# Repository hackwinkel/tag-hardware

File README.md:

# tag-hardware

The "tag" is a cheap badge with a PADAUK PFS154-S16 microcontroller, 24 RGB leds and IR transmitter & receiver for inter-badge communications.
The software/hardware *may* also work with a PMS150C-S16 and pin compatible controllers from other manufacturers (e.g. Nyquest tech), but this is untested

This hardware goes with the software described here: https://github.com/hackwinkel/tag-software

## Background

This badge was originally designed for SMD hotplate soldering workshops at TBD (https://tbd.camp/) and later used for workshops at haxogreen 2024 () and private workshops, and is loosely based on a 2023 version which can be found here: https://github.com/hackwinkel/label-hardware and https://github.com/hackwinkel/label-software

According to internet rule 663829, "Every hacker conference shall have a badge". Being hackers, of course, leads to hypotheses 1-3:
"1: Any hacker conference badge will be overly complex",
"2: Any hacker conference badge will be released with unfinished software" and
"3: Any hacker conference  badge will function poorly for its namesake purpose".
This badge disproves these 3 hypotheses.

## What is in this repository

0) This README
1) a LICENSE file
2) A directory with KiCAD 5 source files
3) A directory with PCB fabrication (Gerber) files produced from these source files
4) A ZIP file containing the Gerber files for PCB fabrication.

If you only want to produce PCBs, you should be able to upload the PCB_fabrication.zip file to your PCB board house directly.
If you want to produce a single stencil, you can use  the PCB_fabrication.zip file - yoor PCB board house will extract the right file from this.

As the board only contains SMD components on the front side, you have to specify that the PCB board house should make a stencil from the "front paste" Gerber file only

## Reprogramming in-circuit

Reprogramming the processor through the programming connection may not work as expected because of failure to calibrate the clock speed while in-circuit. You CAN reprogram the badge without clock-speed calibration by using easypdkprog with the --nocalibrate option.

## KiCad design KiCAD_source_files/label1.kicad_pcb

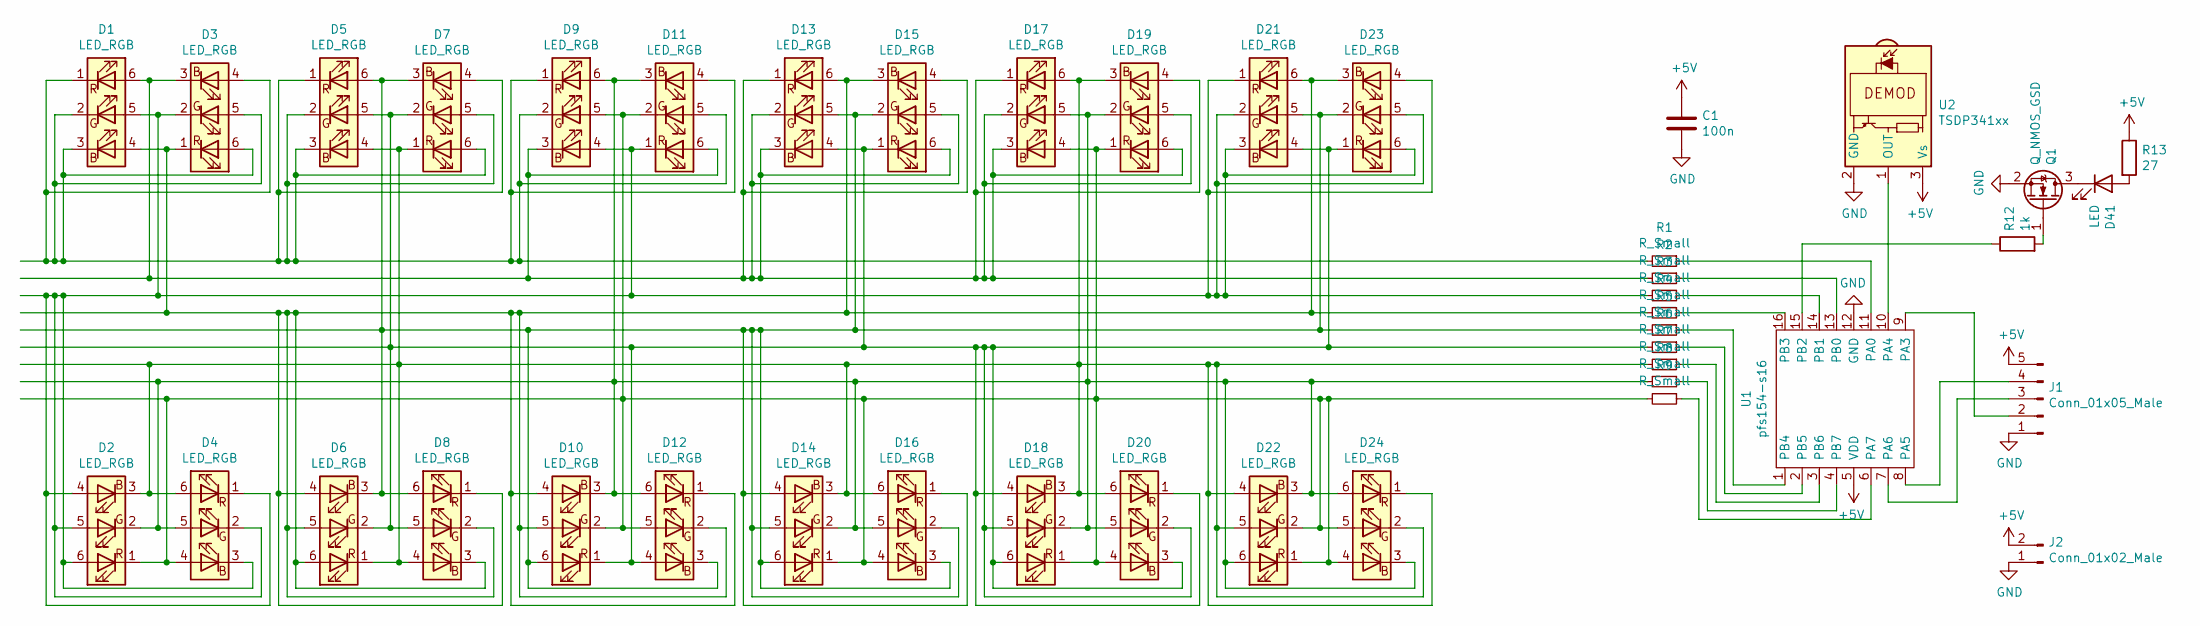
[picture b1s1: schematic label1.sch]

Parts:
C1: 100n; C_0805
D1, D2, D3, D4, D5, D6, D7, D8, D9, D10, D11, D12, D13, D14, D15, D16, D17, D18, D19, D20, D21, D22, D23, D24: LED_RGB
D41: LED; LED_3030
J1: Conn_01x05_Male; PinHeader_1x05
J2: Conn_01x02_Male; battcon
Q1: Q_NMOS_GSD; SOT-23
R1, R2, R3, R4, R5, R6, R7, R8, R9: R_Small; R_0805
R12: 1k; R_0805
R13: 27; R_1206
U1: pfs154-s16; SOP-16
U2: TSDP341xx; IR_RCV_SMD

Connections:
+5V: C1.1, J1.5, J2.2, R13.1, U1.5 (VDD), U2.3 (Vs)
GND: C1.2, J1.1, J2.1, Q1.2 (S), U1.12 (GND), U2.2 (GND)
unnamed: D1.1 (RK), D1.2 (GK), D1.3 (BK), D3.4 (BA), D3.5 (GA), D3.6 (RA), D5.1 (RK), D5.2 (GK), D5.3 (BK), D7.4 (BA), D7.5 (GA), D7.6 (RA), D9.1 (RK), D9.2 (GK), D11.4 (BA), D11.5 (GA), R1.2
unnamed: D1.4 (BA), D3.1 (RK), D6.4 (BA), D6.5 (GA), D6.6 (RA), D8.1 (RK), D8.2 (GK), D8.3 (BK), D10.4 (BA), D10.5 (GA), D12.1 (RK), D12.2 (GK), D13.6 (RA), D15.3 (BK), D21.6 (RA), D23.3 (BK), R4.2
unnamed: D1.5 (GA), D2.4 (BA), D2.5 (GA), D2.6 (RA), D3.2 (GK), D4.1 (RK), D4.2 (GK), D4.3 (BK), D9.4 (BA), D11.1 (RK), D21.1 (RK), D21.2 (GK), D21.3 (BK), D23.4 (BA), D23.5 (GA), D23.6 (RA), R3.2
unnamed: D1.6 (RA), D3.3 (BK), D9.3 (BK), D11.6 (RA), D13.1 (RK), D13.2 (GK), D13.3 (BK), D15.4 (BA), D15.5 (GA), D15.6 (RA), D17.1 (RK), D17.2 (GK), D17.3 (BK), D19.4 (BA), D19.5 (GA), D19.6 (RA), R2.2
unnamed: D5.5 (GA), D6.2 (GK), D7.2 (GK), D8.5 (GA), D10.1 (RK), D12.4 (BA), D13.4 (BA), D15.1 (RK), D18.4 (BA), D18.5 (GA), D18.6 (RA), D20.1 (RK), D20.2 (GK), D20.3 (BK), D21.4 (BA), D23.1 (RK), R6.2
unnamed: D2.1 (RK), D4.4 (BA), D9.5 (GA), D10.2 (GK), D11.2 (GK), D12.5 (GA), D14.1 (RK), D16.4 (BA), D17.4 (BA), D18.1 (RK), D19.1 (RK), D20.4 (BA), D22.1 (RK), D22.2 (GK), D24.4 (BA), D24.5 (GA), R9.2
unnamed: D2.2 (GK), D4.5 (GA), D9.6 (RA), D10.3 (BK), D11.3 (BK), D12.6 (RA), D14.2 (GK), D16.5 (GA), D17.5 (GA), D18.2 (GK), D19.2 (GK), D20.5 (GA), D22.3 (BK), D22.6 (RA), D24.3 (BK), D24.6 (RA), R8.2
unnamed: D5.6 (RA), D6.3 (BK), D7.3 (BK), D8.6 (RA), D10.6 (RA), D12.3 (BK), D13.5 (GA), D14.4 (BA), D14.5 (GA), D14.6 (RA), D15.2 (GK), D16.1 (RK), D16.2 (GK), D16.3 (BK), D21.5 (GA), D23.2 (GK), R5.2
unnamed: D2.3 (BK), D4.6 (RA), D5.4 (BA), D6.1 (RK), D7.1 (RK), D8.4 (BA), D14.3 (BK), D16.6 (RA), D17.6 (RA), D18.3 (BK), D19.3 (BK), D20.6 (RA), D22.4 (BA), D22.5 (GA), D24.1 (RK), D24.2 (GK), R7.2
unnamed: D41.1 (K), Q1.3 (D)
unnamed: D41.2 (A), R13.2
unnamed: J1.2, U1.9 (PA3)
unnamed: J1.3, U1.7 (PA6)
unnamed: J1.4, U1.8 (PA5)
unnamed: Q1.1 (G), R12.2
unnamed: R1.1, U1.11 (PA0)
unnamed: R2.1, U1.13 (PB0)
unnamed: R3.1, U1.14 (PB1)
unnamed: R4.1, U1.16 (PB3)
unnamed: R5.1, U1.1 (PB4)
unnamed: R6.1, U1.2 (PB5)
unnamed: R7.1, U1.3 (PB6)
unnamed: R8.1, U1.4 (PB7)
unnamed: R9.1, U1.6 (PA7)
unnamed: R12.1, U1.15 (PB2)
unnamed: U1.10 (PA4), U2.1 (OUT)

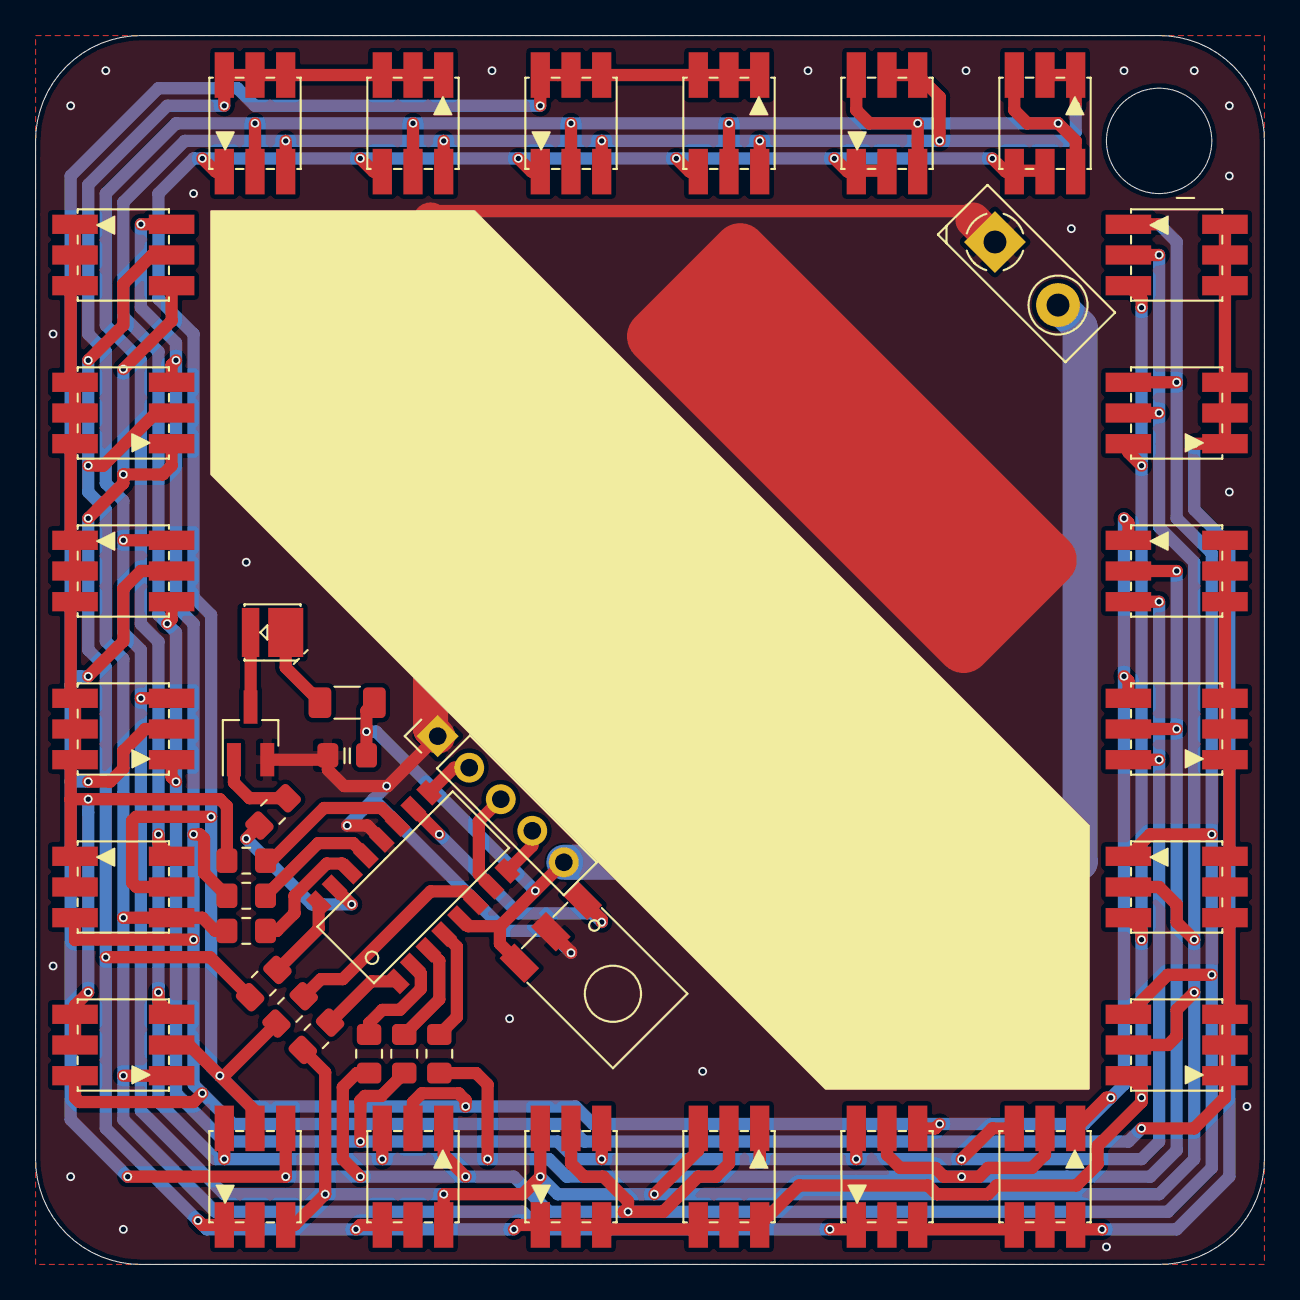
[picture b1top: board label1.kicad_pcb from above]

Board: 2 copper layers, 70.0 x 70.0 mm, 42 parts (0 on the bottom side), 28 nets.

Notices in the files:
KiCAD_source_files/label1.kicad_pcb:
(c)2024 Theo Borm
